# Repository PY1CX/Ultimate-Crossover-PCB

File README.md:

# Ultimate-Crossover-PCB

This is a Crossover PCB that I designed for my own use, it uses the Linkwitz-Riley topology so you can design your own filter with any software that calculates the Linkwitz-Riley topology.

You can make with this board:
- Subwoofer low pass filter with Stereo Input adder
- Two way Filter
- Bandpass Filter
- Everything else that you can imagine

Use at your own risk, if you make a professional PCB please send me a e-mail and send me one as a gift :) 

If find any bugs let me know or send a review via git.

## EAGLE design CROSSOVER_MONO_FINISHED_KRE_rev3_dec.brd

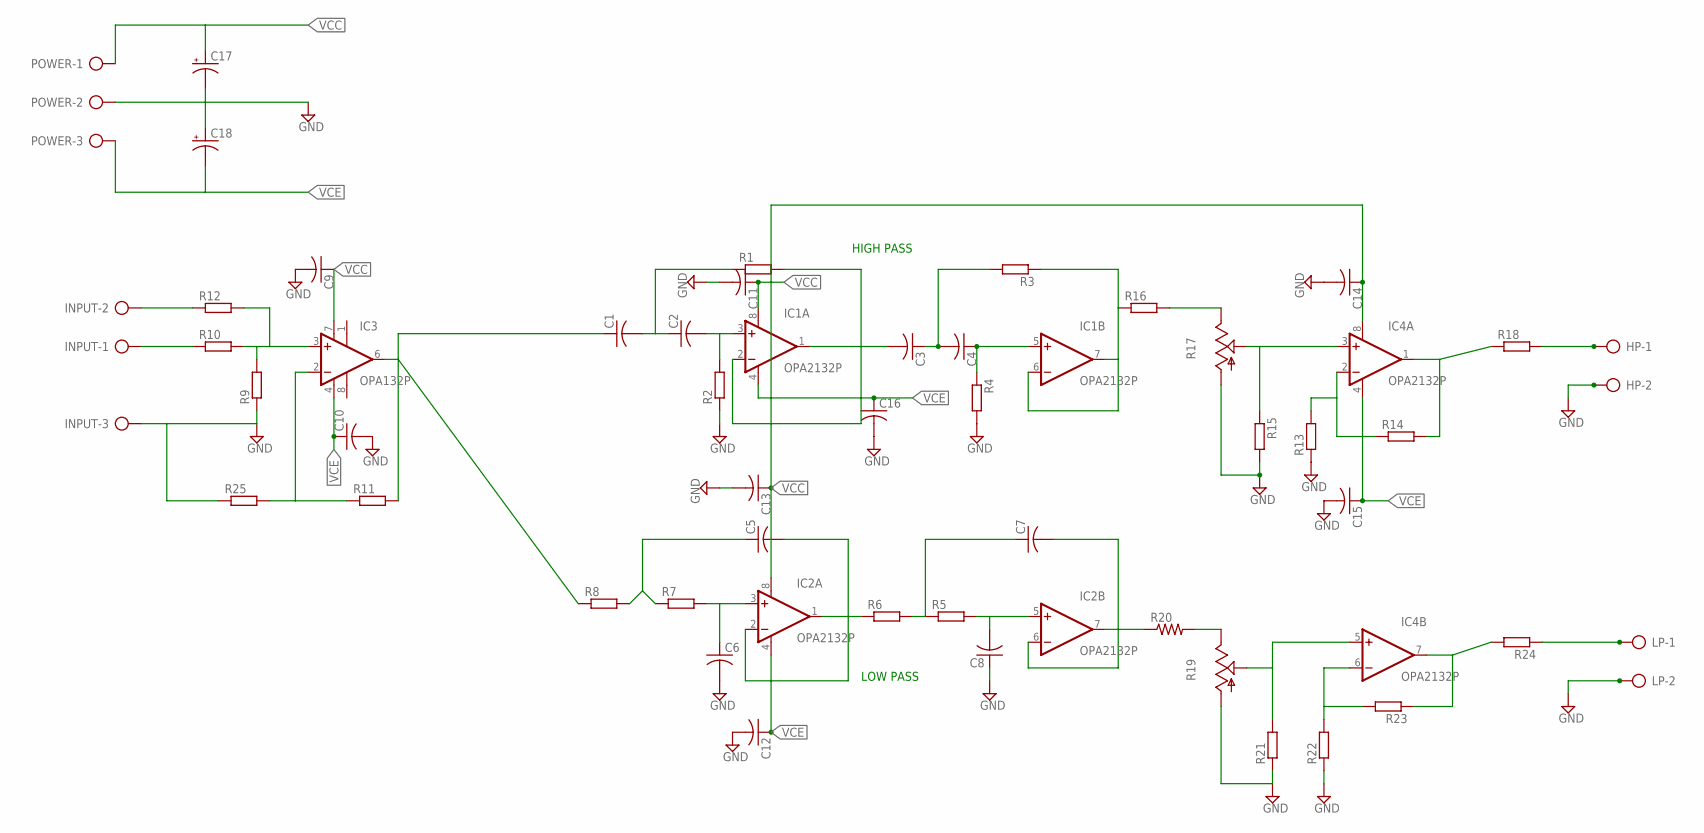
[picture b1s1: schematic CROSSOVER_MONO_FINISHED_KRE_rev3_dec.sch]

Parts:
C1, C2, C3, C4, C5, C6, C7, C8, C9, C10, C11, C12, C13, C14, C15, C16: C-US050-025X075; C050-025X075
C17, C18: CPOL-USE5-10.5; E5-10,5
HP: KRE_2VIAS
IC1, IC2, IC4: OPA2132P; DIL08
IC3: OPA132P; DIL08
INPUT: KRE_3VIAS
LP: KRE_2VIAS
POWER: KRE_3VIAS
R1, R2, R3, R4, R5, R6, R7, R8, R9, R10, R11, R12, R13, R14, R15, R16, R18, R21, R22, R23, R24, R25: R-EU_0207/10; 0207/10
R17, R19: TRIM_US-RJ9W; RJ9W
R20: R-US_0204/7; 0204/7

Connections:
GND: C6.2, C8.1, C9.2, C10.2, C11.2, C12.2, C13.2, C14.2, C15.2, C16.2, C17.-, C18.+, HP.2, INPUT.3, LP.2, POWER.2, R2.1, R4.2, R9.1, R13.1, R15.2, R17.A, R19.A, R21.1, R22.1, R25.1
unnamed: C3.1, C4.2, R3.2
unnamed: C5.2, IC2.1 (OUT), IC2.2 (-IN), R6.1
unnamed: C6.1, IC2.3 (+IN), R7.2
unnamed: C5.1, R7.1, R8.2
unnamed: C7.2, IC2.6 (-IN), IC2.7 (OUT), R20.1
unnamed: C7.1, R5.1, R6.2
unnamed: C8.2, IC2.5 (+IN), R5.2
unnamed: IC1.6 (-IN), IC1.7 (OUT), R3.1, R16.1
unnamed: C2.2, IC1.3 (+IN), R2.2
unnamed: C4.1, IC1.5 (+IN), R4.1
unnamed: C3.2, IC1.1 (OUT), IC1.2 (-IN), R1.2
unnamed: C1.1, IC3.6 (OUT), R8.1, R11.2
unnamed: C1.2, C2.1, R1.1
unnamed: IC3.3 (+IN), R9.2, R10.2, R12.2
unnamed: INPUT.1, R10.1
unnamed: IC3.2 (-IN), R11.1, R25.2
unnamed: INPUT.2, R12.1
unnamed: IC4.1 (OUT), R14.2, R18.1
unnamed: IC4.2 (-IN), R13.2, R14.1
unnamed: R16.2, R17.E
unnamed: IC4.3 (+IN), R15.1, R17.S
unnamed: HP.1, R18.2
unnamed: R19.E, R20.2
unnamed: LP.1, R24.1
unnamed: IC4.7 (OUT), R23.1, R24.2
unnamed: IC4.6 (-IN), R22.2, R23.2
unnamed: IC4.5 (+IN), R19.S, R21.2
VCC: C9.1, C11.1, C13.1, C14.1, C17.+, IC1.8 (V+), IC2.8 (V+), IC3.7 (V+), IC4.8 (V+), POWER.1
VCE: C10.1, C12.1, C15.1, C16.1, C18.-, IC1.4 (V-), IC2.4 (V-), IC3.4 (V-), IC4.4 (V-), POWER.3

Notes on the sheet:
LOW PASS
HIGH PASS

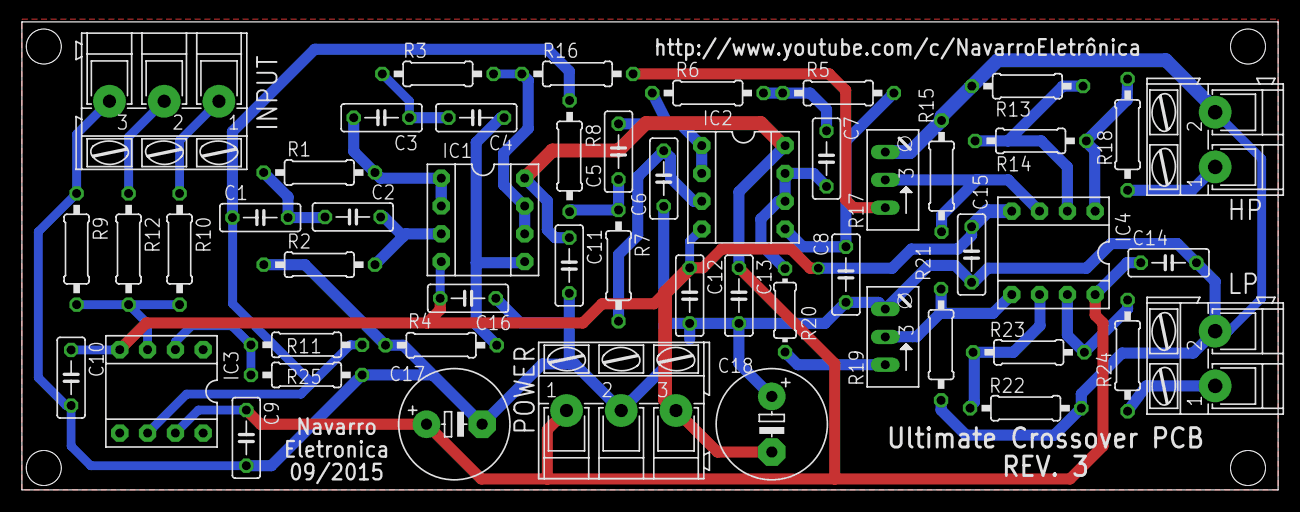
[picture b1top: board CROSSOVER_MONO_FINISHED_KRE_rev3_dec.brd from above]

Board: 2 copper layers, 114.8 x 42.8 mm, 51 parts (0 on the bottom side), 30 nets.

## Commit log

2015-12-02 First commit of the third revision
